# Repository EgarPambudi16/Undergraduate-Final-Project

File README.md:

# Undergraduate-Final-Project
Progress Repository of Undergraduate Final Project by Egar Pambudi

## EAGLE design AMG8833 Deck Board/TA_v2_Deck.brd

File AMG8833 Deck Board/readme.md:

<b>Crazyflie AMG8833-ESP32 Deck Board</b></br>

Custom made Crazyflie Deck features AMG8833 Thermal Array Sensor and ESP32-C3-12F</br>
Board include separated vertical ESP32 board, AMG8833's attachment pinhead, and JST-PH 2.0 pin for programming

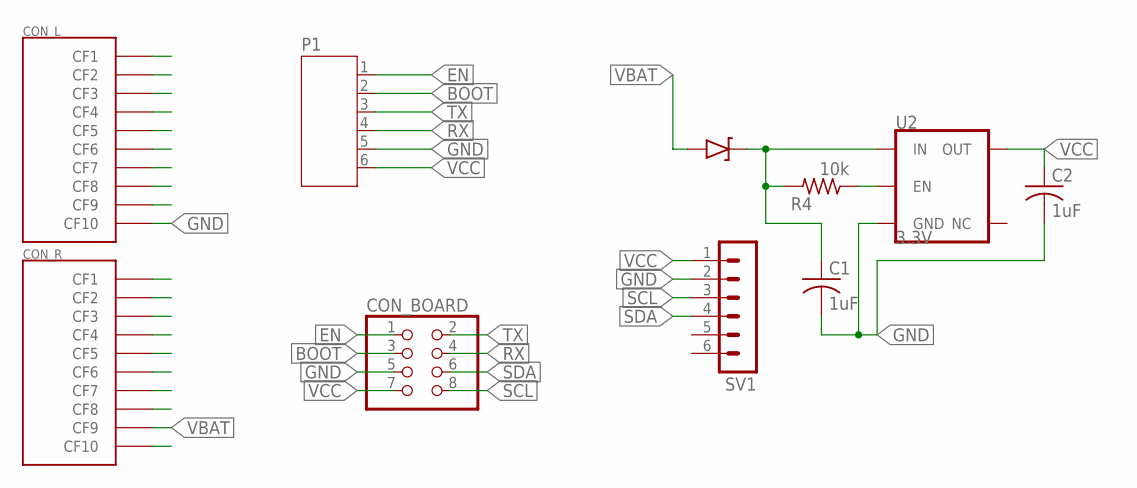
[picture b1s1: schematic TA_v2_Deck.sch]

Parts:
C1, C2: 1uF; C0805
CON_BOARD: PINHD-2X4; 2X04
CON_L: FEMALE_CON; FEMALE_HEADER_2
CON_R: FEMALE_CON; FEMALE_HEADER_2
P1: JST-PH6
R4: 10k; R0603
SV1: MA06-1
U2: 3.3V; SOT23-5
U$2: 1N5819; SOT-323

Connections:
BOOT: CON_BOARD.3, P1.2
EN: CON_BOARD.1, P1.1
GND: C1.2, C2.2, CON_BOARD.5, CON_L.CF10, P1.5, SV1.2, U2.2 (GND)
unnamed: C1.1, R4.2, U2.1 (IN), U$2.K
unnamed: R4.1, U2.3 (EN)
RX: CON_BOARD.4, P1.4
SCL: CON_BOARD.8, SV1.3
SDA: CON_BOARD.6, SV1.4
TX: CON_BOARD.2, P1.3
VBAT: CON_R.CF9, U$2.A
VCC: C2.1, CON_BOARD.7, P1.6, SV1.1, U2.5 (OUT)

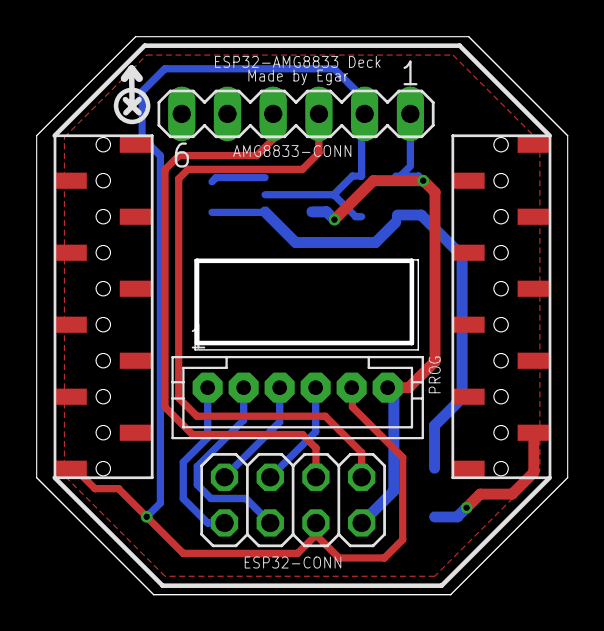
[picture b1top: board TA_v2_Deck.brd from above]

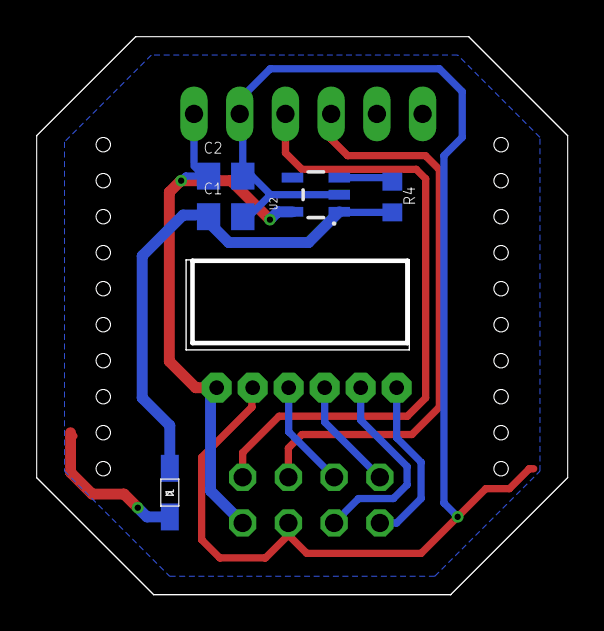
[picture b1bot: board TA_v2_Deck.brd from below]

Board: 2 copper layers, 29.3 x 30.8 mm, 10 parts (5 on the bottom side), 11 nets.

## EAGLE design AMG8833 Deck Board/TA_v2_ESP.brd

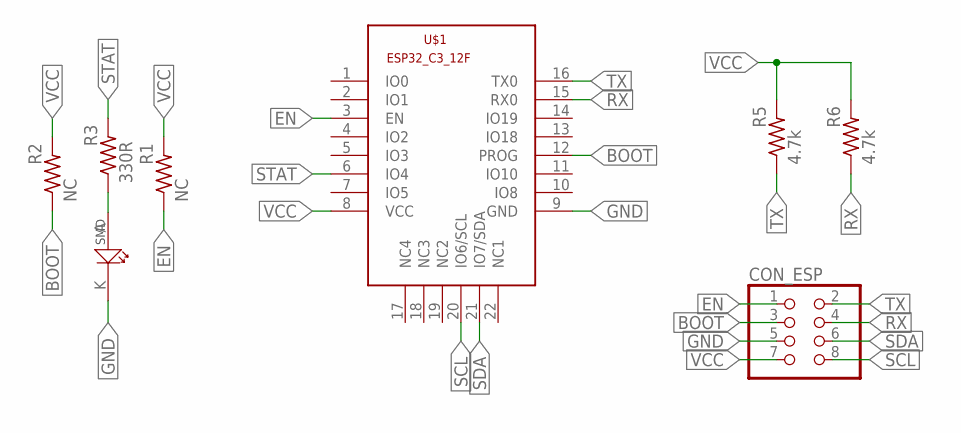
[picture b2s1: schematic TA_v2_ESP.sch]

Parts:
CON_ESP: PINHD-2X4; 2X04
R1, R2: NC; R0603
R3: 330R; R0603
R5, R6: 4.7k; R0603
U$1: ESP32-C3-12FESP32-C3-12F; ESP32-C3-12F
U$3: LED_SMD; LED_0603

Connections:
BOOT: CON_ESP.3, R2.1, U$1.12 (PROG)
EN: CON_ESP.1, R1.1, U$1.3 (EN)
GND: CON_ESP.5, U$1.9 (GND), U$3.K
unnamed: R3.1, U$3.A
RX: CON_ESP.4, R6.1, U$1.15 (RX0)
SCL: CON_ESP.8, U$1.20 (IO6/SCL)
SDA: CON_ESP.6, U$1.21 (IO7/SDA)
STAT: R3.2, U$1.6 (IO4)
TX: CON_ESP.2, R5.1, U$1.16 (TX0)
VCC: CON_ESP.7, R1.2, R2.2, R5.2, R6.2, U$1.8 (VCC)

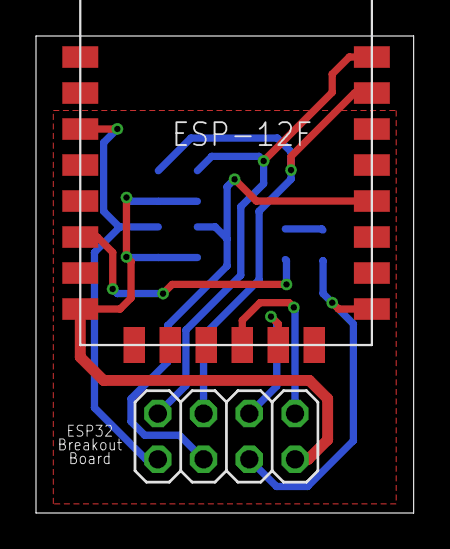
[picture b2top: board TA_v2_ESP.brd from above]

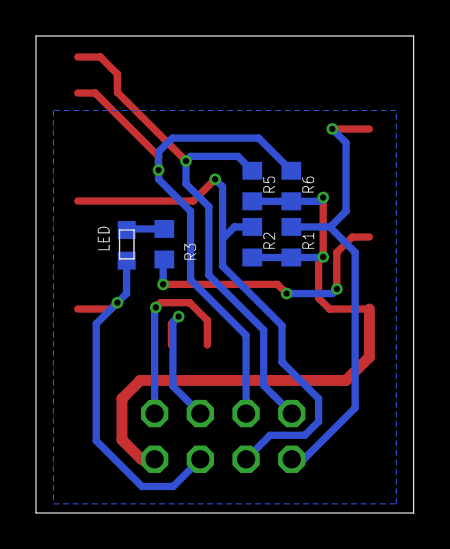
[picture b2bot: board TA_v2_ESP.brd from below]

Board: 2 copper layers, 21.0 x 26.5 mm, 8 parts (6 on the bottom side), 10 nets.

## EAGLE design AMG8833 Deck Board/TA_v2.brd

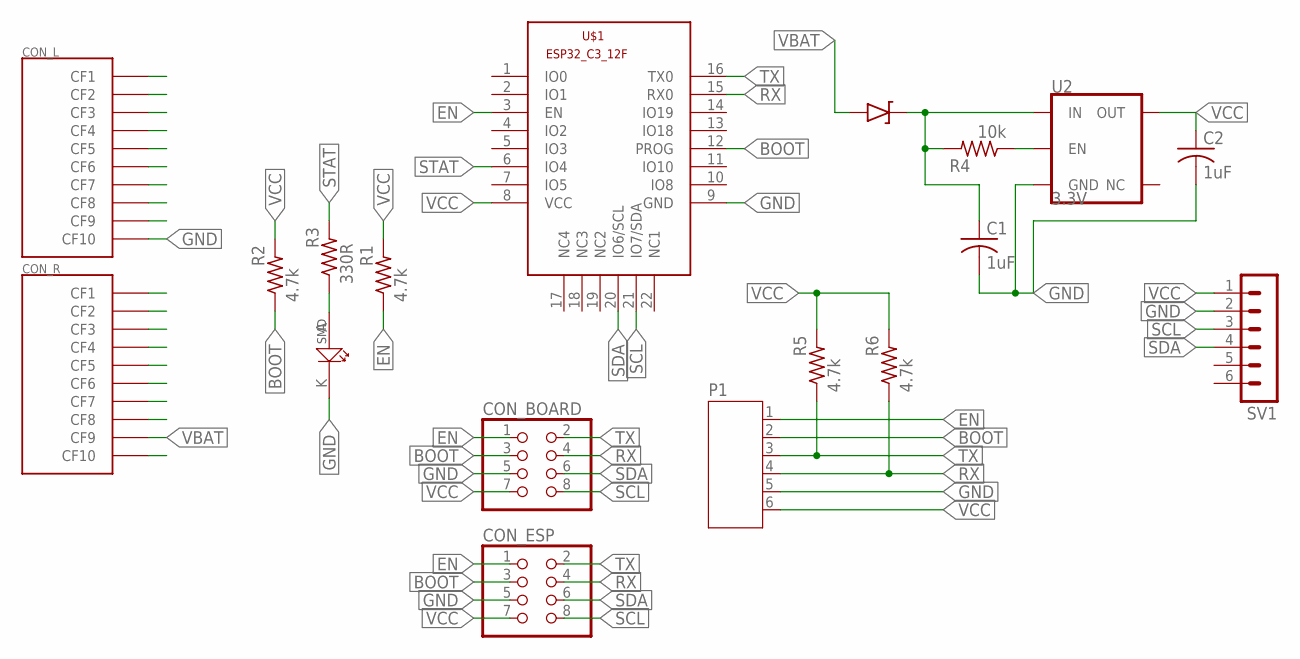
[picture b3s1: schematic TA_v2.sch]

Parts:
C1, C2: 1uF; C0805
CON_BOARD: PINHD-2X4; 2X04
CON_ESP: PINHD-2X4; 2X04
CON_L: FEMALE_CON; FEMALE_HEADER_2
CON_R: FEMALE_CON; FEMALE_HEADER_2
P1: JST-PH6
R1, R2, R5, R6: 4.7k; R0603
R3: 330R; R0603
R4: 10k; R0603
SV1: MA06-1
U2: 3.3V; SOT23-5
U$1: ESP32-C3-12FESP32-C3-12F; ESP32-C3-12F
U$2: 1N5819; SOT-323
U$3: LED_SMD; LED_0603

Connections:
BOOT: CON_BOARD.3, CON_ESP.3, P1.2, R2.1, U$1.12 (PROG)
EN: CON_BOARD.1, CON_ESP.1, P1.1, R1.1, U$1.3 (EN)
GND: C1.2, C2.2, CON_BOARD.5, CON_ESP.5, CON_L.CF10, P1.5, SV1.2, U2.2 (GND), U$1.9 (GND), U$3.K
unnamed: C1.1, R4.2, U2.1 (IN), U$2.K
unnamed: R4.1, U2.3 (EN)
unnamed: R3.1, U$3.A
RX: CON_BOARD.4, CON_ESP.4, P1.4, R6.1, U$1.15 (RX0)
SCL: CON_BOARD.8, CON_ESP.8, SV1.3, U$1.21 (IO7/SDA)
SDA: CON_BOARD.6, CON_ESP.6, SV1.4, U$1.20 (IO6/SCL)
STAT: R3.2, U$1.6 (IO4)
TX: CON_BOARD.2, CON_ESP.2, P1.3, R5.1, U$1.16 (TX0)
VBAT: CON_R.CF9, U$2.A
VCC: C2.1, CON_BOARD.7, CON_ESP.7, P1.6, R1.2, R2.2, R5.2, R6.2, SV1.1, U2.5 (OUT), U$1.8 (VCC)

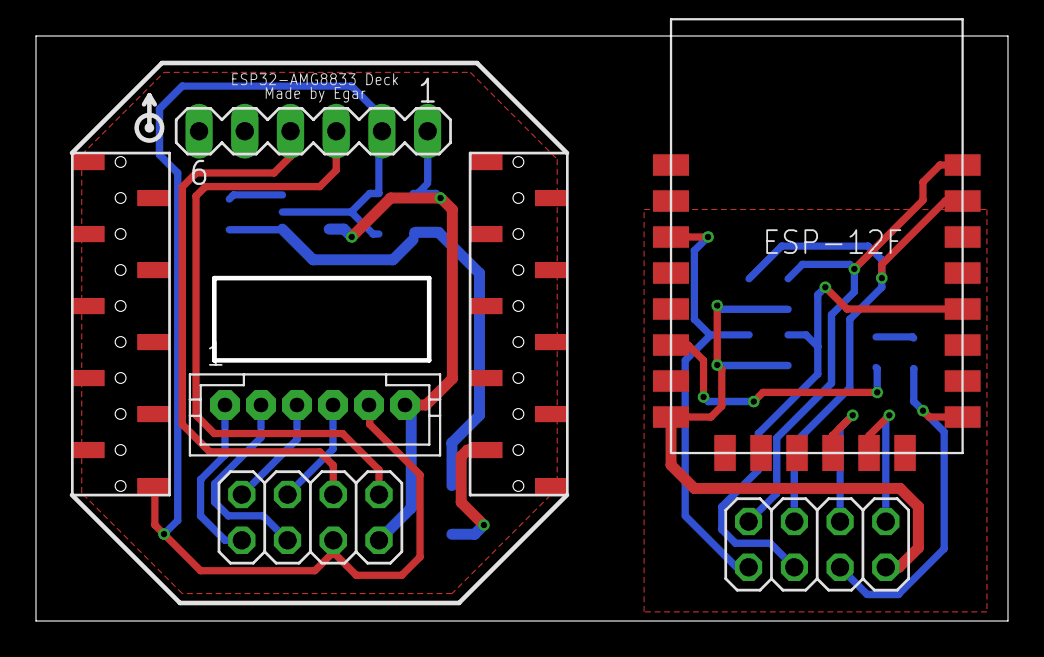
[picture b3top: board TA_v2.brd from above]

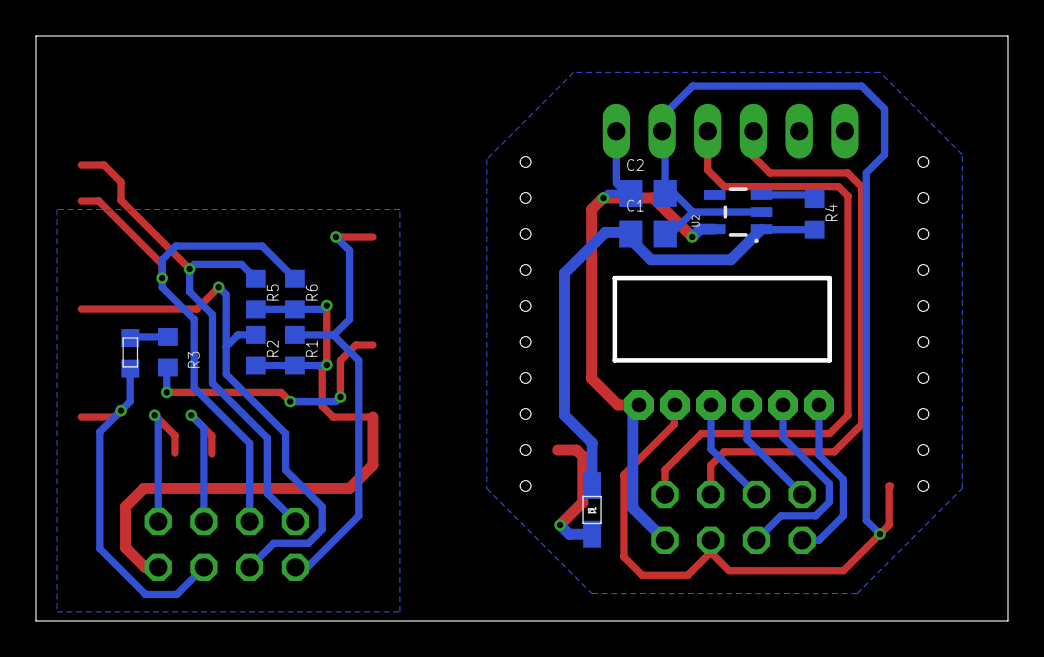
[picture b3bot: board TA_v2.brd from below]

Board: 2 copper layers, 53.7 x 32.2 mm, 18 parts (11 on the bottom side), 13 nets.

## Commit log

2022-10-27 Add schematic file TA_V2.sch
2022-10-27 Added EAGLE Board File TA_v2.brd
2022-10-27 Add EAGLE library files
2022-10-27 Update TA_v2.brd
    Update AMG8833 Deck Board design, change part placement, library update, dimension update, added milling and copper pour area
2022-10-27 Add Gerber files
2022-10-27 Rename readme.txt to readme.md
2022-10-27 Add files via upload
    Split board between Deck and ESP Board
2022-11-02 Add AMG Deck Code and python main code
2022-11-17 main.py code update, adding thermal detection
2022-11-22 Fix Board Design
2022-12-12 Add new function for plotting
